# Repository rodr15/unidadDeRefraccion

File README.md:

# ursmart

A new Flutter project.

## Getting Started

This project is a starting point for a Flutter application.

A few resources to get you started if this is your first Flutter project:

- [Lab: Write your first Flutter app](https://flutter.dev/docs/get-started/codelab)
- [Cookbook: Useful Flutter samples](https://flutter.dev/docs/cookbook)

For help getting started with Flutter, view our
[online documentation](https://flutter.dev/docs), which offers tutorials,
samples, guidance on mobile development, and a full API reference.

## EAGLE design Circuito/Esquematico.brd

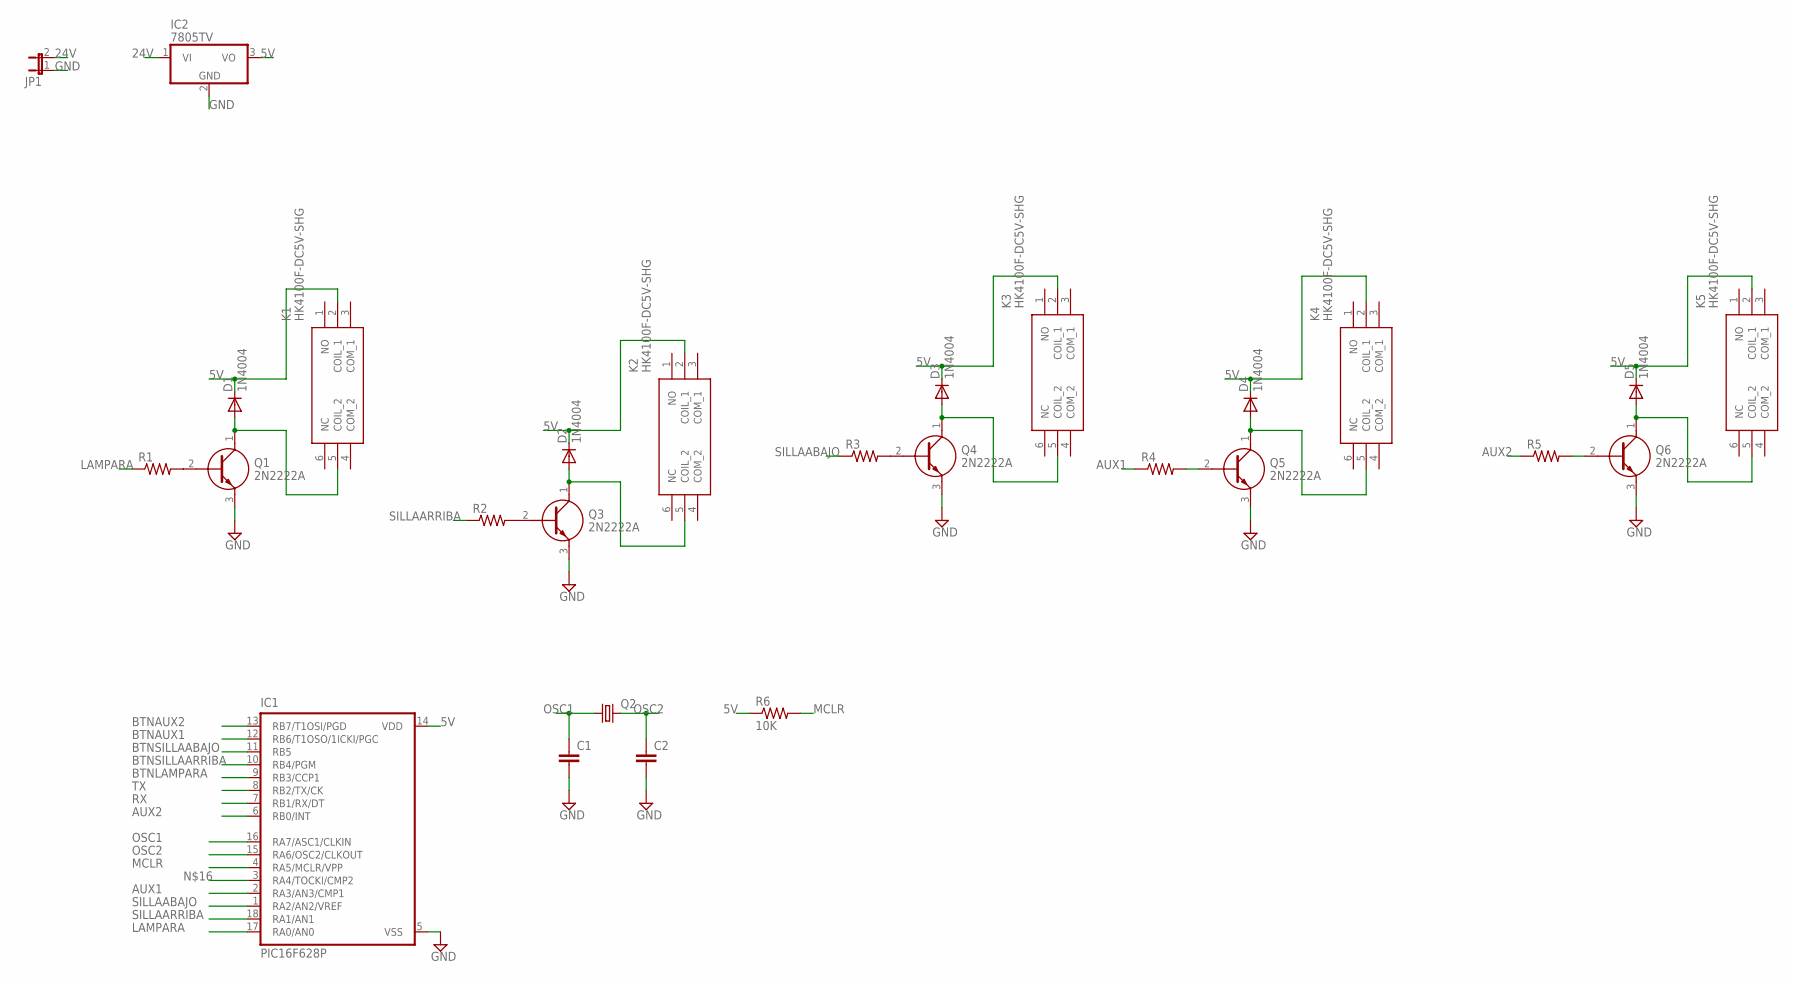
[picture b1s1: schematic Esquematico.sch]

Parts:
C1, C2: C2,5-3; C2.5-3
D1, D2, D3, D4, D5: 1N4004; DO41-10
IC1: PIC16F628P; DIL18
IC2: 7805TV; TO220V
JP1: JP1E; JP1
K1, K2, K3, K4, K5: HK4100F-DC5V-SHG; HK4100FDC5VSHG
Q1, Q3, Q4, Q5, Q6: 2N2222A
Q2: CRYSTALHC49U70; HC49U70
R1, R2, R3, R4, R5: R-US_0207/7; 0207/7
R6: 10K; 0207/7

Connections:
5V: D1.C, D2.C, D3.C, D4.C, D5.C, IC1.14 (VDD), IC2.3 (VO), K1.2 (COIL_1), K2.2 (COIL_1), K3.2 (COIL_1), K4.2 (COIL_1), K5.2 (COIL_1), R6.1
24V: IC2.1 (VI), JP1.2
AUX1: IC1.2 (RA3/AN3/CMP1), R4.1
AUX2: IC1.6 (RB0/INT), R5.1
BTNAUX1: IC1.12 (RB6/T1OSO/1ICKI/PGC)
BTNAUX2: IC1.13 (RB7/T1OSI/PGD)
BTNLAMPARA: IC1.9 (RB3/CCP1)
BTNSILLAABAJO: IC1.11 (RB5)
BTNSILLAARRIBA: IC1.10 (RB4/PGM)
GND: C1.2, C2.2, IC1.5 (VSS), IC2.2 (GND), JP1.1, Q1.3 (E), Q3.3 (E), Q4.3 (E), Q5.3 (E), Q6.3 (E)
LAMPARA: IC1.17 (RA0/AN0), R1.1
MCLR: IC1.4 (RA5/MCLR/VPP), R6.2
unnamed: Q1.2 (B), R1.2
unnamed: D1.A, K1.5 (COIL_2), Q1.1 (C)
unnamed: Q3.2 (B), R2.2
unnamed: D2.A, K2.5 (COIL_2), Q3.1 (C)
unnamed: Q4.2 (B), R3.2
unnamed: D3.A, K3.5 (COIL_2), Q4.1 (C)
unnamed: Q5.2 (B), R4.2
unnamed: D4.A, K4.5 (COIL_2), Q5.1 (C)
unnamed: Q6.2 (B), R5.2
unnamed: D5.A, K5.5 (COIL_2), Q6.1 (C)
OSC1: C1.1, IC1.16 (RA7/ASC1/CLKIN), Q2.1
OSC2: C2.1, IC1.15 (RA6/OSC2/CLKOUT), Q2.2
RX: IC1.7 (RB1/RX/DT)
SILLAABAJO: IC1.1 (RA2/AN2/VREF), R3.1
SILLAARRIBA: IC1.18 (RA1/AN1), R2.1
TX: IC1.8 (RB2/TX/CK)

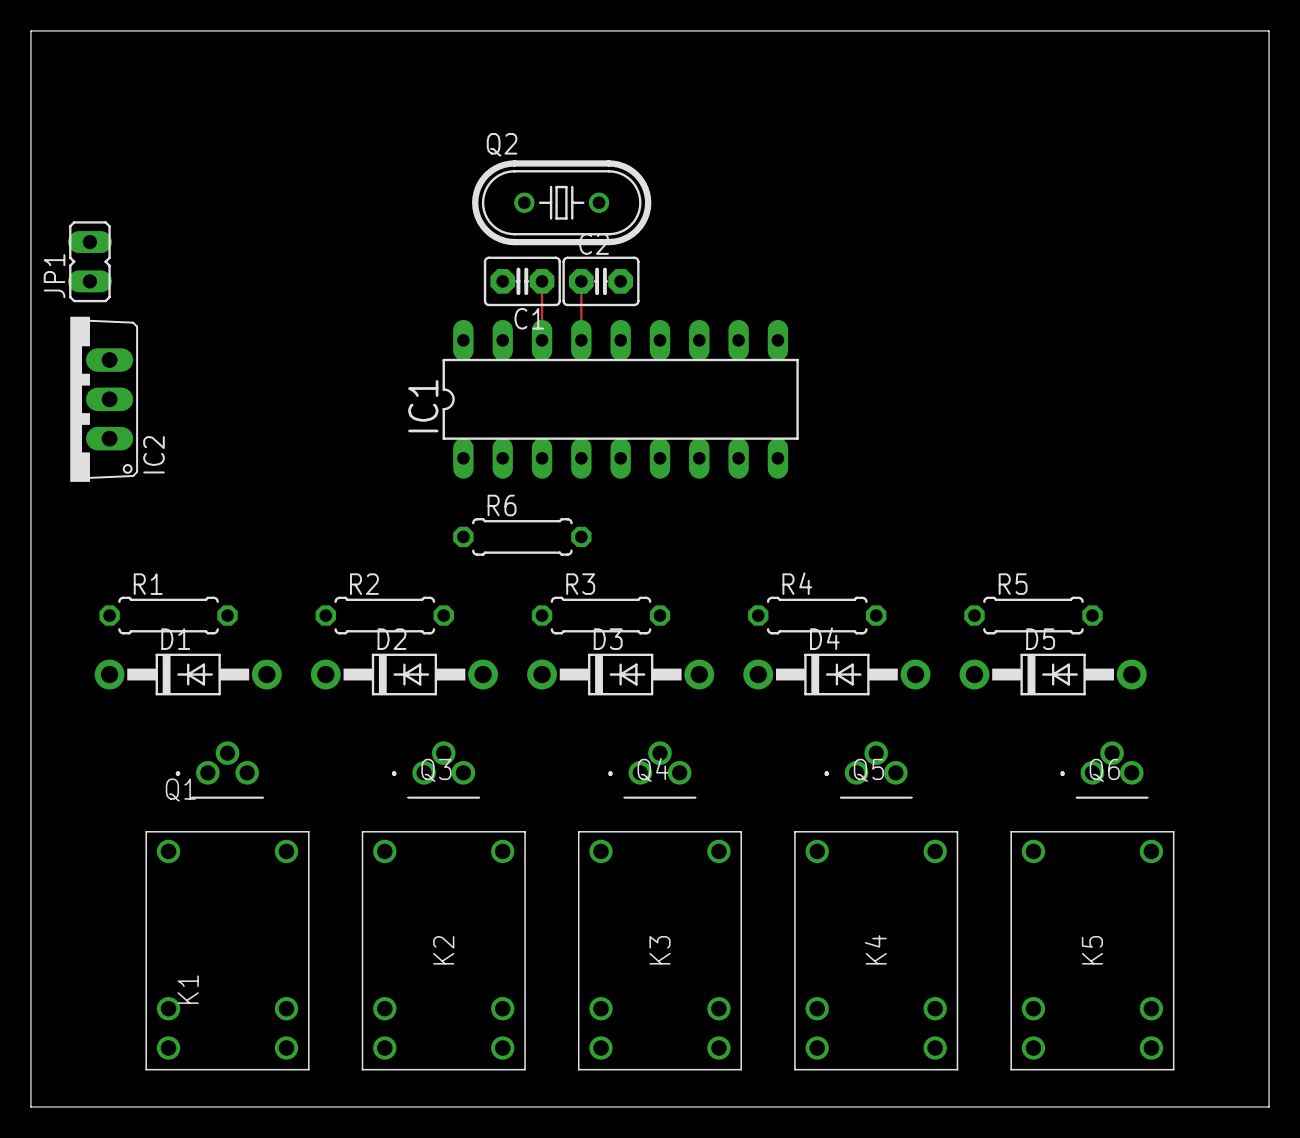
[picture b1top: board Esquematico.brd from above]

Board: 2 copper layers, 80.0 x 69.5 mm, 27 parts (0 on the bottom side), 21 nets.

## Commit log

2022-04-07 Inicio aplicacion
2022-04-08 Botones
2022-04-11 Permisos del bluetooth
2022-04-21 Funcionando bluetooth
2022-05-11 Inicio del circuito
